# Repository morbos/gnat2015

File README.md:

gnat2015 for Hercules RM46 and RM57
             -----------------------------------

0) This tree contains the gnat2015 full and sfp ravenscar libs ported
to the Hercules RM46 and RM57 processors.

1) The code is specifically targeted to the 2 launchpad boards for
both the devices.

2) For each devices, there is an example that has 2 tasks that each
toggle and LED and an overall loop that prints at 115200 8N1 to the
LIN1 UART port.

3) To build this, first go to libre.adacore.com and DL gnat2015 tools
for ARM (choose your host, Windows or Linux).

4) Add the bin dir to your path.

5) Build the lib of interest: (example here is rm57, similar for rm46)

% cd gnat2015/ravenscar-full-rm57
% gprbuild

If all is well, you will have a library.

For the sfp lib the build is as so:

% cd gnat2015/ravenscar-sfp-rm57
% gprbuild ravenscar_build.gpr

6) Build an example (example here is rm57, similar for rm46)

% cd gnat2015/hercules/RM57/example
% make

There will be a demo.out in the obj dir that UniFlash can program.

7) Connect a UART and observe the output (also the LEDs will be
toggling).

8) GDB and beyond.

If you want to source level debug, 
a) acquire a pod, I use a JLINK clone for $10-$15 on ebay. 
b) DL openocd 0.9 

c) prepare your board for JTAG debug. You will need a Samtec
connector soldered down:

ftr-110-51-s-d-06

d) A JTAG adaper is needed. JLINK official sells these, they
convert ARM20 to CTI-20.

https://www.segger.com/jlink-adapters.html#TI20

e) DL openocd 0.9

f) Use the openocd target and board files provided.

g) You should be able to start openocd and see the target

openocd --file ti_rm57launchpad.cfg

root@bplus:~/openocd-0.9.0/tcl# ../src/openocd --file

board/ti_rm57launchpad.cfg

Open On-Chip Debugger 0.9.0 (2015-05-31-20:38)

Licensed under GNU GPL v2

For bug reports, read

        http://openocd.org/doc/doxygen/bugs.html

adapter speed: 1000 kHz

adapter speed: 1000 kHz

Info : auto-selecting first available session transport "jtag". To

override use       'transport select <transport>'.

Warn : rm57.dap: nonstandard IR mask

force hard breakpoints

trst_only separate trst_push_pull

Info : J-Link ARM V8 compiled Dec  6 2011 18:57:44

Info : J-Link caps 0xb9ff7bbf

Info : J-Link hw version 80000

Info : J-Link hw type J-Link

Info : J-Link max mem block 9440

Info : J-Link configuration

Info : USB-Address: 0x0

Info : Kickstart power on JTAG-pin 19: 0xffffffff

Info : Vref = 3.384 TCK = 1 TDI = 0 TDO = 0 TMS = 0 SRST = 1 TRST =
1

Info : J-Link JTAG Interface ready

Info : clock speed 1000 kHz

Info : JTAG tap: rm57.jrc tap/device found: 0x0b95a02f (mfg: 0x017,

part: 0xb95a      , ver: 0x0)

Info : JTAG tap: rm57.dap enabled

Info : rm57.cpu: hardware has 8 breakpoints, 8 watchpoints

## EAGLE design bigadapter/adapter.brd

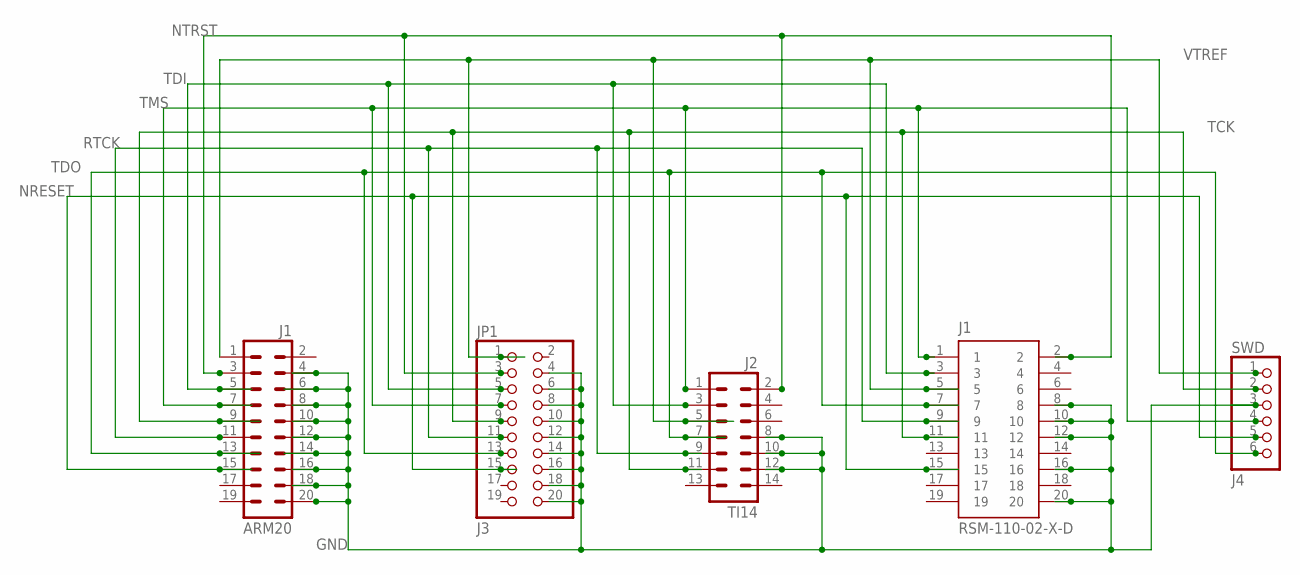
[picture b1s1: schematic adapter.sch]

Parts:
ARM20: J1; ML20
J1: RSM-110-02-X-D
JP1: J3; 2X10
SWD: J4; 1X06
TI14: J2; ML14

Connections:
GND: ARM20.4, ARM20.6, ARM20.8, ARM20.10, ARM20.12, ARM20.14, ARM20.16, ARM20.18, ARM20.20, J1.8, J1.10, J1.12, J1.16, J1.20, JP1.4, JP1.6, JP1.8, JP1.10, JP1.12, JP1.14, JP1.16, JP1.18, JP1.20, SWD.3, TI14.8, TI14.10, TI14.12
NRESET: ARM20.15, J1.15, JP1.15, SWD.5
NTRST: ARM20.3, J1.2, JP1.3, TI14.2
RTCK: ARM20.11, J1.9, JP1.11, TI14.9
TCK: ARM20.9, J1.11, JP1.9, SWD.2, TI14.11
TDI: ARM20.5, J1.3, JP1.5, TI14.3
TDO: ARM20.13, J1.7, JP1.13, SWD.6, TI14.7
TMS: ARM20.7, J1.1, JP1.7, SWD.4, TI14.1
VTREF: ARM20.1, J1.5, JP1.1, SWD.1, TI14.5

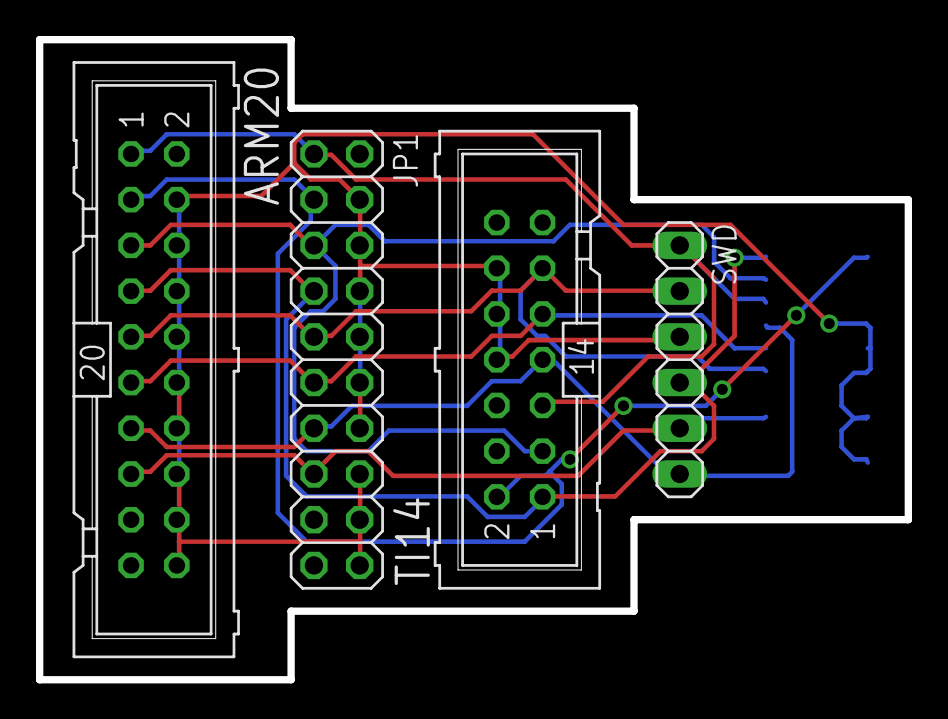
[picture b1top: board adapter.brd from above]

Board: 2 copper layers, 48.3 x 35.6 mm, 5 parts (0 on the bottom side), 9 nets.

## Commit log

2015-06-30 Initial
2015-06-30 symlink cull
2015-06-30 README fixes
2015-11-25 Fixed ravenscar-sfp-rm46 runtime project file.
    Deleted "math" from Source_Dirs list. Directory math is not included in the ravenscar-sfp-rm46 directory and runtime project wouldn't build.
2015-11-25 Math dir is empty. Cull the ref to it.
2016-02-23 Add JTAG board.
